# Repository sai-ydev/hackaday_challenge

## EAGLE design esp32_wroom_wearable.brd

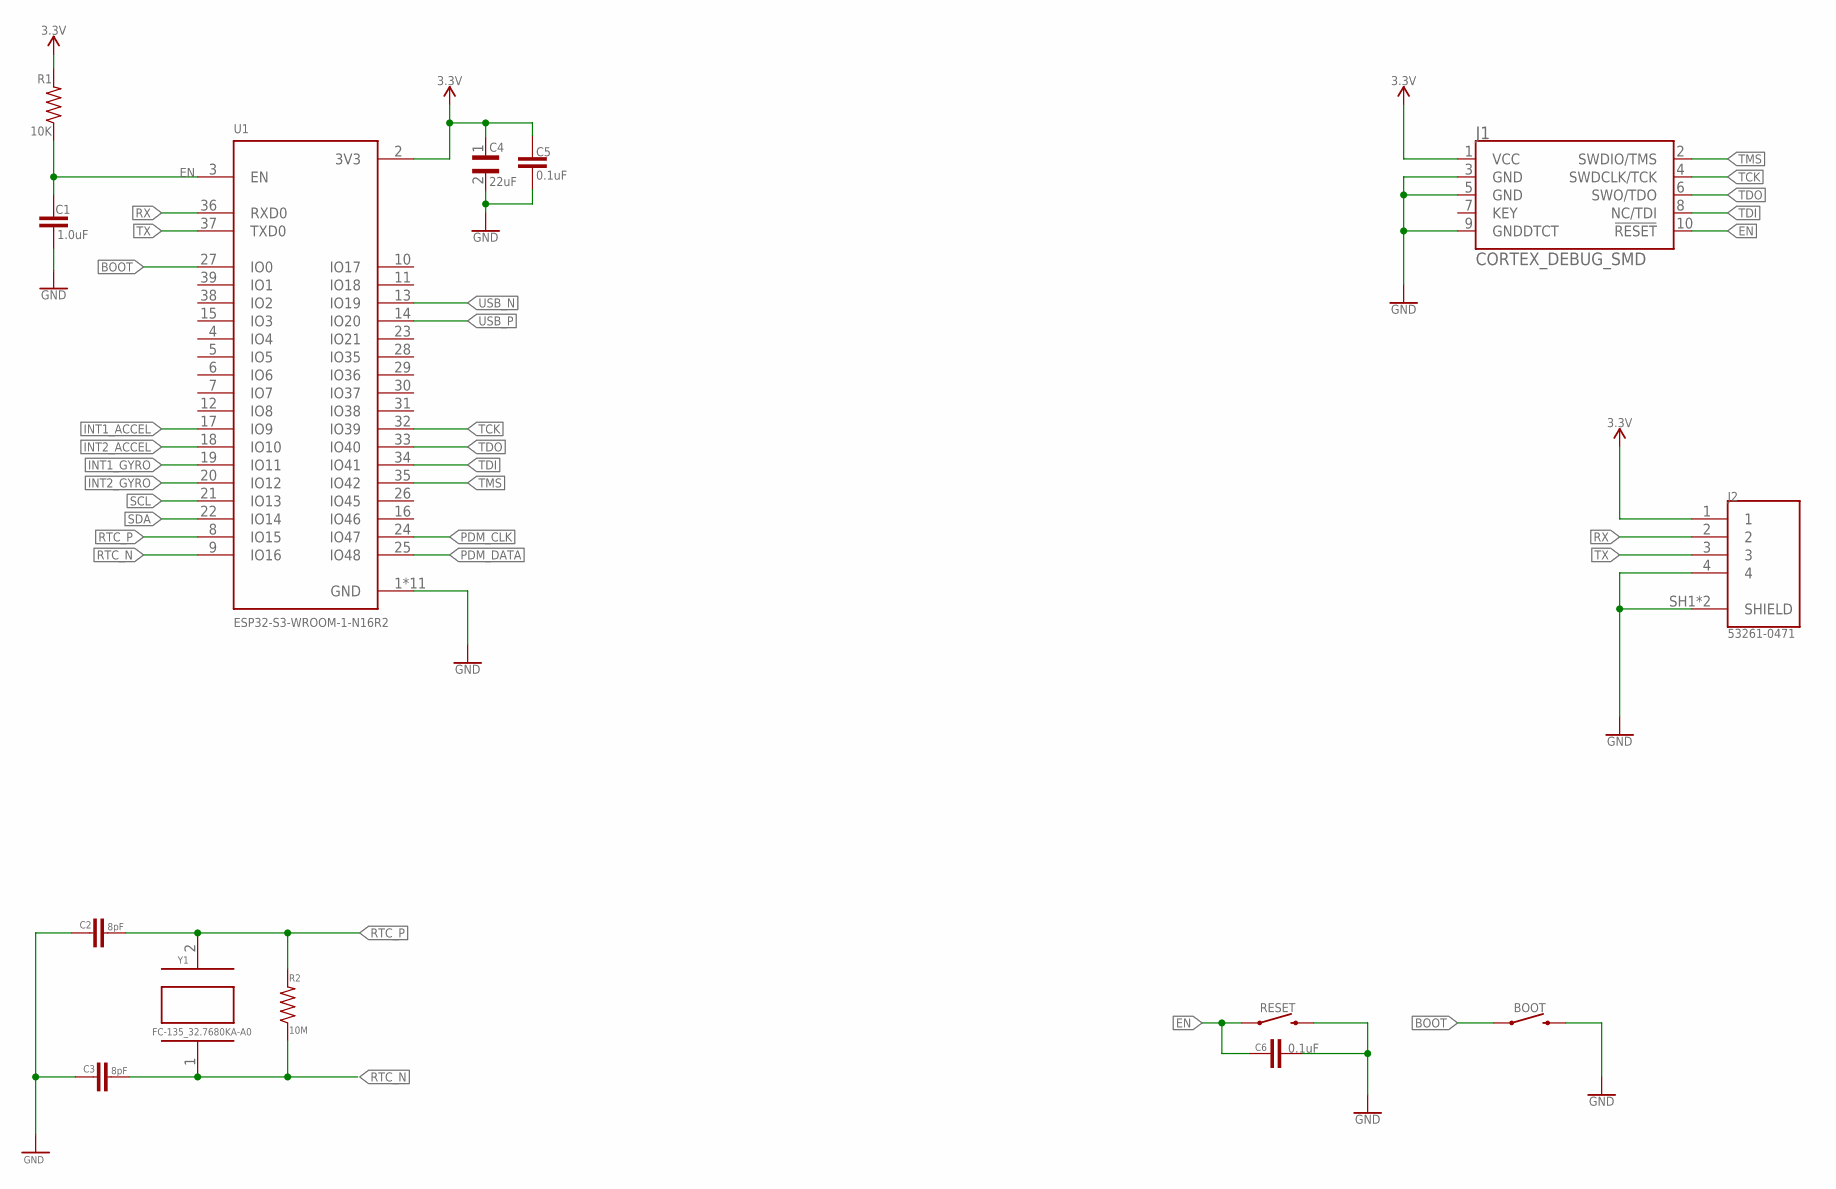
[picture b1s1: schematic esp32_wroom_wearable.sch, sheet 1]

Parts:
BOOT: MOMENTARY-SWITCH-SPST-SMD-4.6X2.8MM; TACTILE_SWITCH_SMD_4.6X2.8MM
C1: 1.0uF; 0402
C2, C3: 8pF; 0402
C4: 22uF; CAPC1005X71N
C5, C6: 0.1uF; 0402
J1: CORTEX_DEBUG_SMD; SAMTECH_FTSH-105-01
J2: 53261-0471; MOLEX_53261-0471
R1: 10K; 0402
R2: 10M; 0402
RESET: MOMENTARY-SWITCH-SPST-SMD-4.6X2.8MM; TACTILE_SWITCH_SMD_4.6X2.8MM
U1: ESP32-S3-WROOM-1-N16R2; XCVR_ESP32-S3-WROOM-1-N16R2
Y1: FC-135_32.7680KA-A0; XTAL_FC-135_32.7680KA-A0

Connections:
3.3V: C4.1, C5.1, J1.1 (VCC), J2.1, R1.2, U1.2 (3V3); also elsewhere on the board
BOOT: BOOT.1, BOOT.2 (1), U1.27 (IO0)
EN: C1.1, C6.1, J1.10 (!RESET), R1.1, RESET.1, RESET.2 (1), U1.3 (EN)
GND: BOOT.3 (2), BOOT.4 (2), C1.2, C2.1, C3.1, C4.2, C5.2, C6.2, J1.3 (GND), J1.5 (GND), J1.9 (GNDDTCT), J2.4, J2.SH1 (SHIELD), J2.SH2 (SHIELD), RESET.3 (2), RESET.4 (2), U1.1 (GND), U1.40 (GND), U1.41_1 (GND), U1.41_2 (GND), U1.41_3 (GND), U1.41_4 (GND), U1.41_5 (GND), U1.41_6 (GND), U1.41_7 (GND), U1.41_8 (GND), U1.41_9 (GND); also elsewhere on the board
INT1_ACCEL: U1.17 (IO9); also elsewhere on the board
INT1_GYRO: U1.19 (IO11); also elsewhere on the board
INT2_ACCEL: U1.18 (IO10); also elsewhere on the board
INT2_GYRO: U1.20 (IO12); also elsewhere on the board
PDM_CLK: U1.24 (IO47); also elsewhere on the board
PDM_DATA: U1.25 (IO48); also elsewhere on the board
RTC_N: C3.2, R2.1, U1.9 (IO16), Y1.1
RTC_P: C2.2, R2.2, U1.8 (IO15), Y1.2
RX: J2.2, U1.36 (RXD0)
SCL: U1.21 (IO13); also elsewhere on the board
SDA: U1.22 (IO14); also elsewhere on the board
TCK: J1.4 (SWDCLK/TCK), U1.32 (IO39)
TDI: J1.8 (NC/TDI), U1.34 (IO41)
TDO: J1.6 (SWO/TDO), U1.33 (IO40)
TMS: J1.2 (SWDIO/TMS), U1.35 (IO42)
TX: J2.3, U1.37 (TXD0)
USB_N: U1.13 (IO19); also elsewhere on the board
USB_P: U1.14 (IO20); also elsewhere on the board

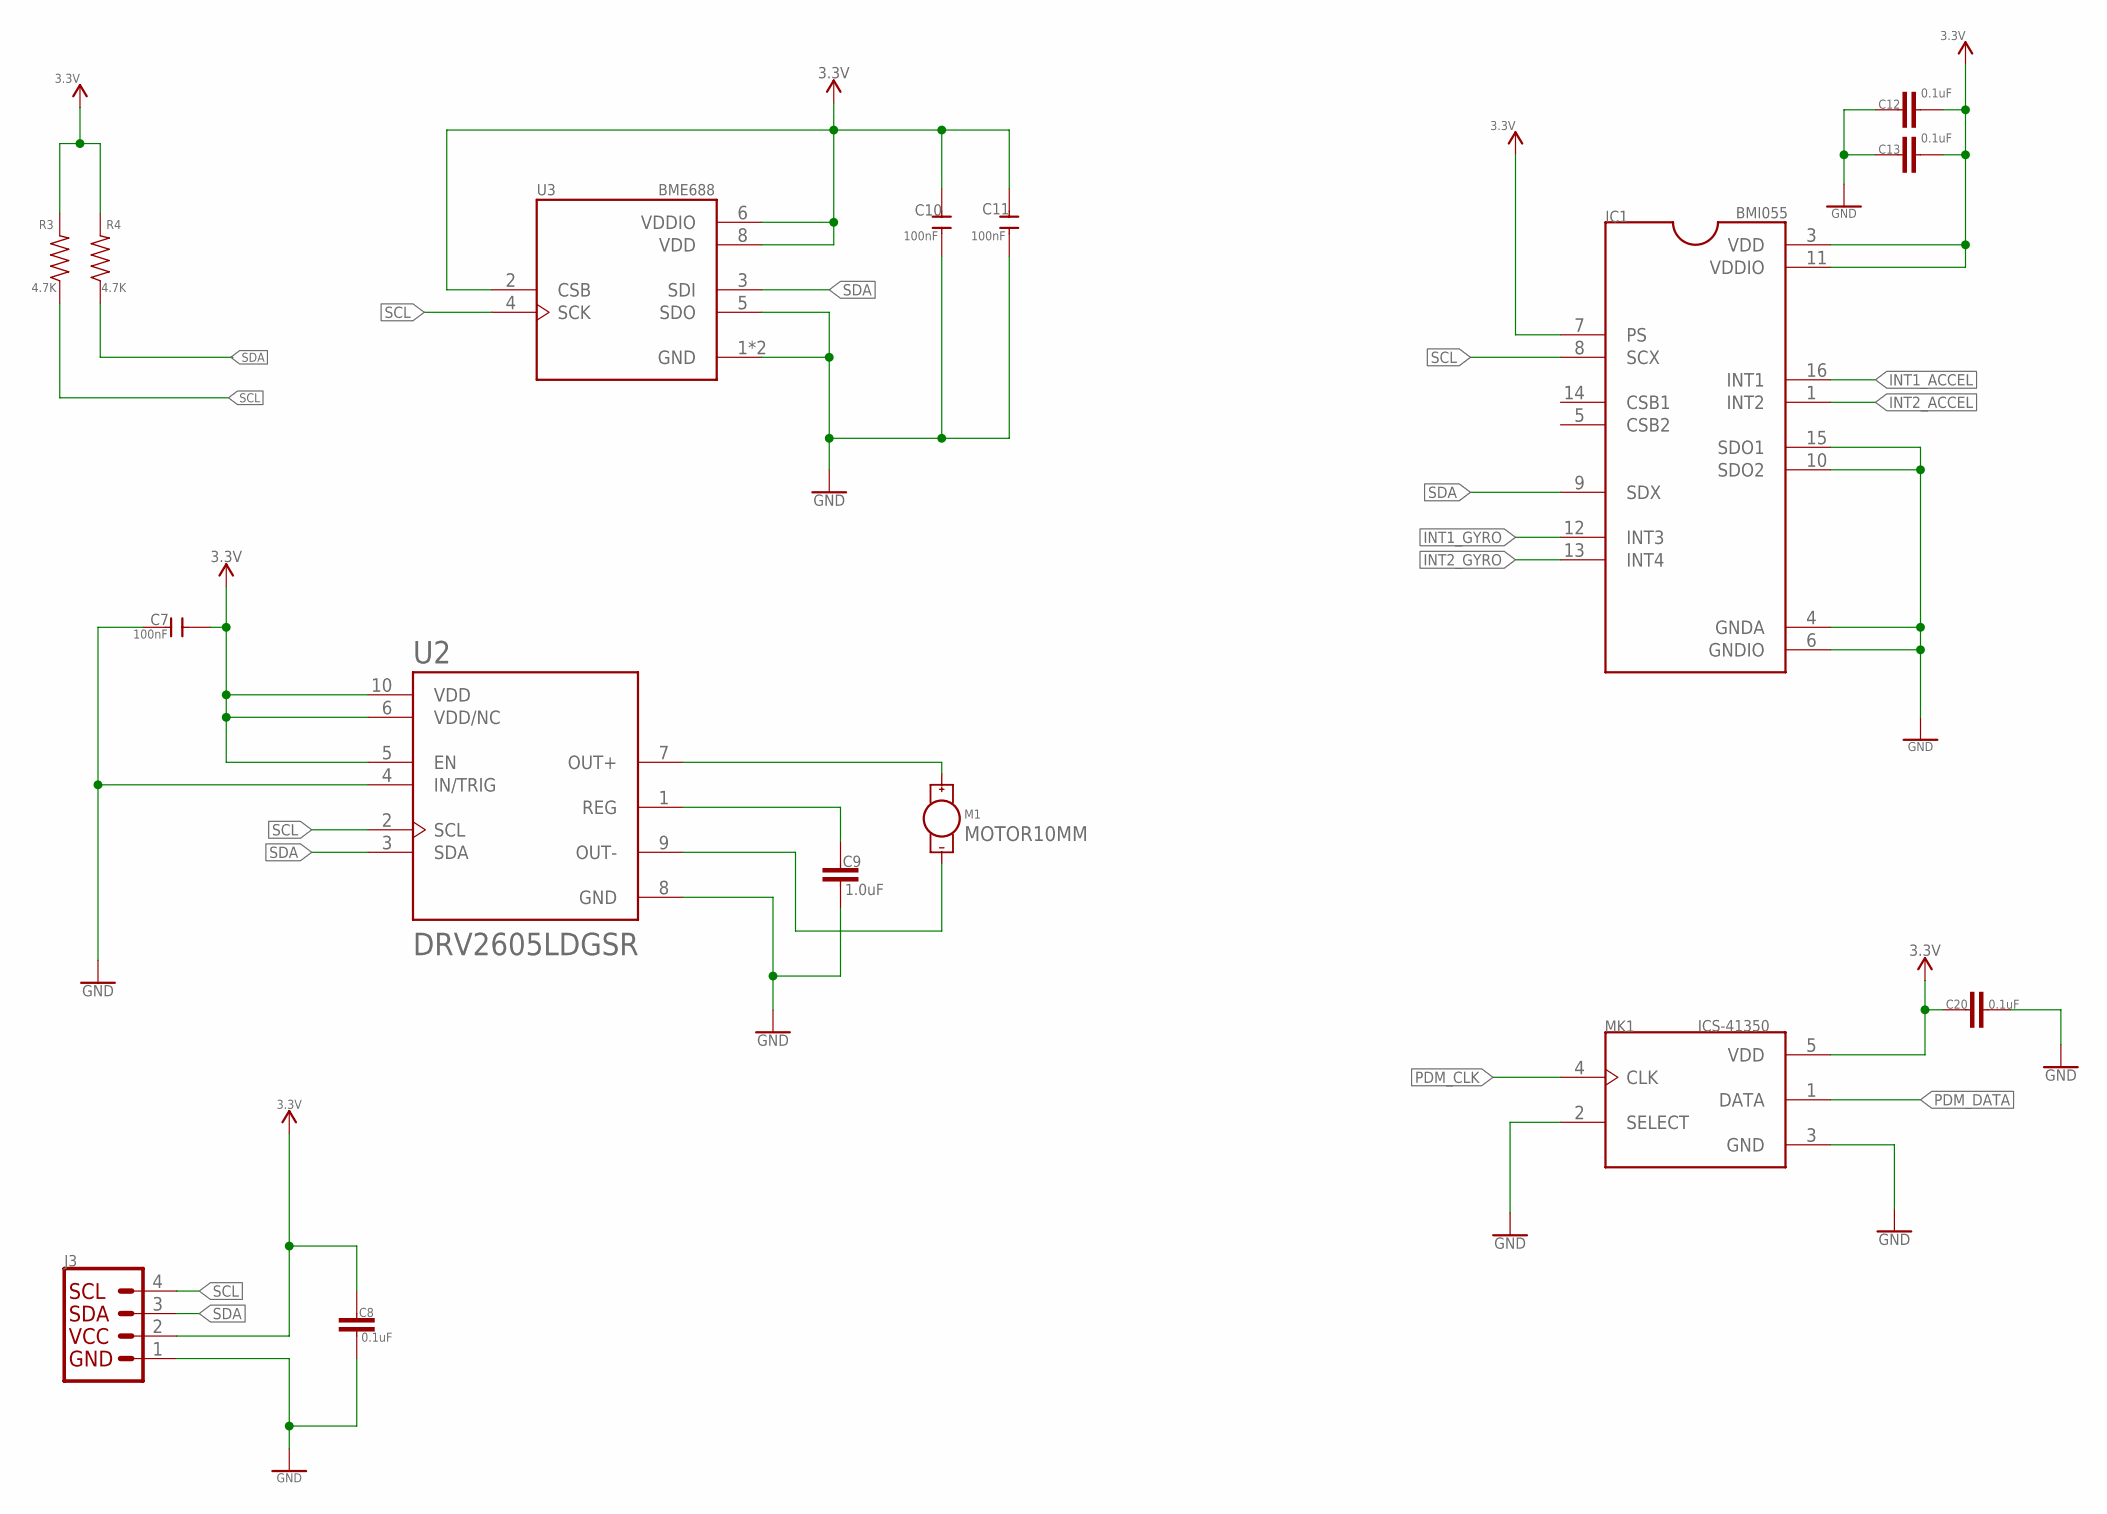
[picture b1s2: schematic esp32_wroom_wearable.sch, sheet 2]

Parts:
C7, C10, C11: 100nF; C0402
C8, C12, C13, C20: 0.1uF; 0402
C9: 1.0uF; 0402
IC1: BMI055; QFN50P300X450X100-16N
J3: QWIIC_CONNECTORJS-1MM; 1X04_1MM_RA
M1: MOTOR10MM; VIBE-MOTOR-10MM
MK1: ICS-41350; MIC_ICS-41350
R3, R4: 4.7K; 0402
U2: DRV2605LDGSR; SOP50P490X110-10N
U3: BME688; IC_BME688

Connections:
3.3V: C7.2, C8.1, C10.1, C11.1, C12.2, C13.2, C20.1, IC1.3 (VDD), IC1.7 (PS), IC1.11 (VDDIO), J3.2, MK1.5 (VDD), R3.2, R4.2, U2.5 (EN), U2.6 (VDD/NC), U2.10 (VDD), U3.2 (CSB), U3.6 (VDDIO), U3.8 (VDD); also elsewhere on the board
GND: C7.1, C8.2, C9.2, C10.2, C11.2, C12.1, C13.1, C20.2, IC1.4 (GNDA), IC1.6 (GNDIO), IC1.10 (SDO2), IC1.15 (SDO1), J3.1, MK1.2 (SELECT), MK1.3 (GND), U2.4 (IN/TRIG), U2.8 (GND), U3.1 (GND), U3.5 (SDO), U3.7 (GND); also elsewhere on the board
INT1_ACCEL: IC1.16 (INT1); also elsewhere on the board
INT1_GYRO: IC1.12 (INT3); also elsewhere on the board
INT2_ACCEL: IC1.1 (INT2); also elsewhere on the board
INT2_GYRO: IC1.13 (INT4); also elsewhere on the board
unnamed: C9.1, U2.1 (REG)
unnamed: M1.+, U2.7 (OUT+)
unnamed: M1.-, U2.9 (OUT-)
PDM_CLK: MK1.4 (CLK); also elsewhere on the board
PDM_DATA: MK1.1 (DATA); also elsewhere on the board
SCL: IC1.8 (SCX), J3.4, R3.1, U2.2 (SCL), U3.4 (SCK); also elsewhere on the board
SDA: IC1.9 (SDX), J3.3, R4.1, U2.3 (SDA), U3.3 (SDI); also elsewhere on the board

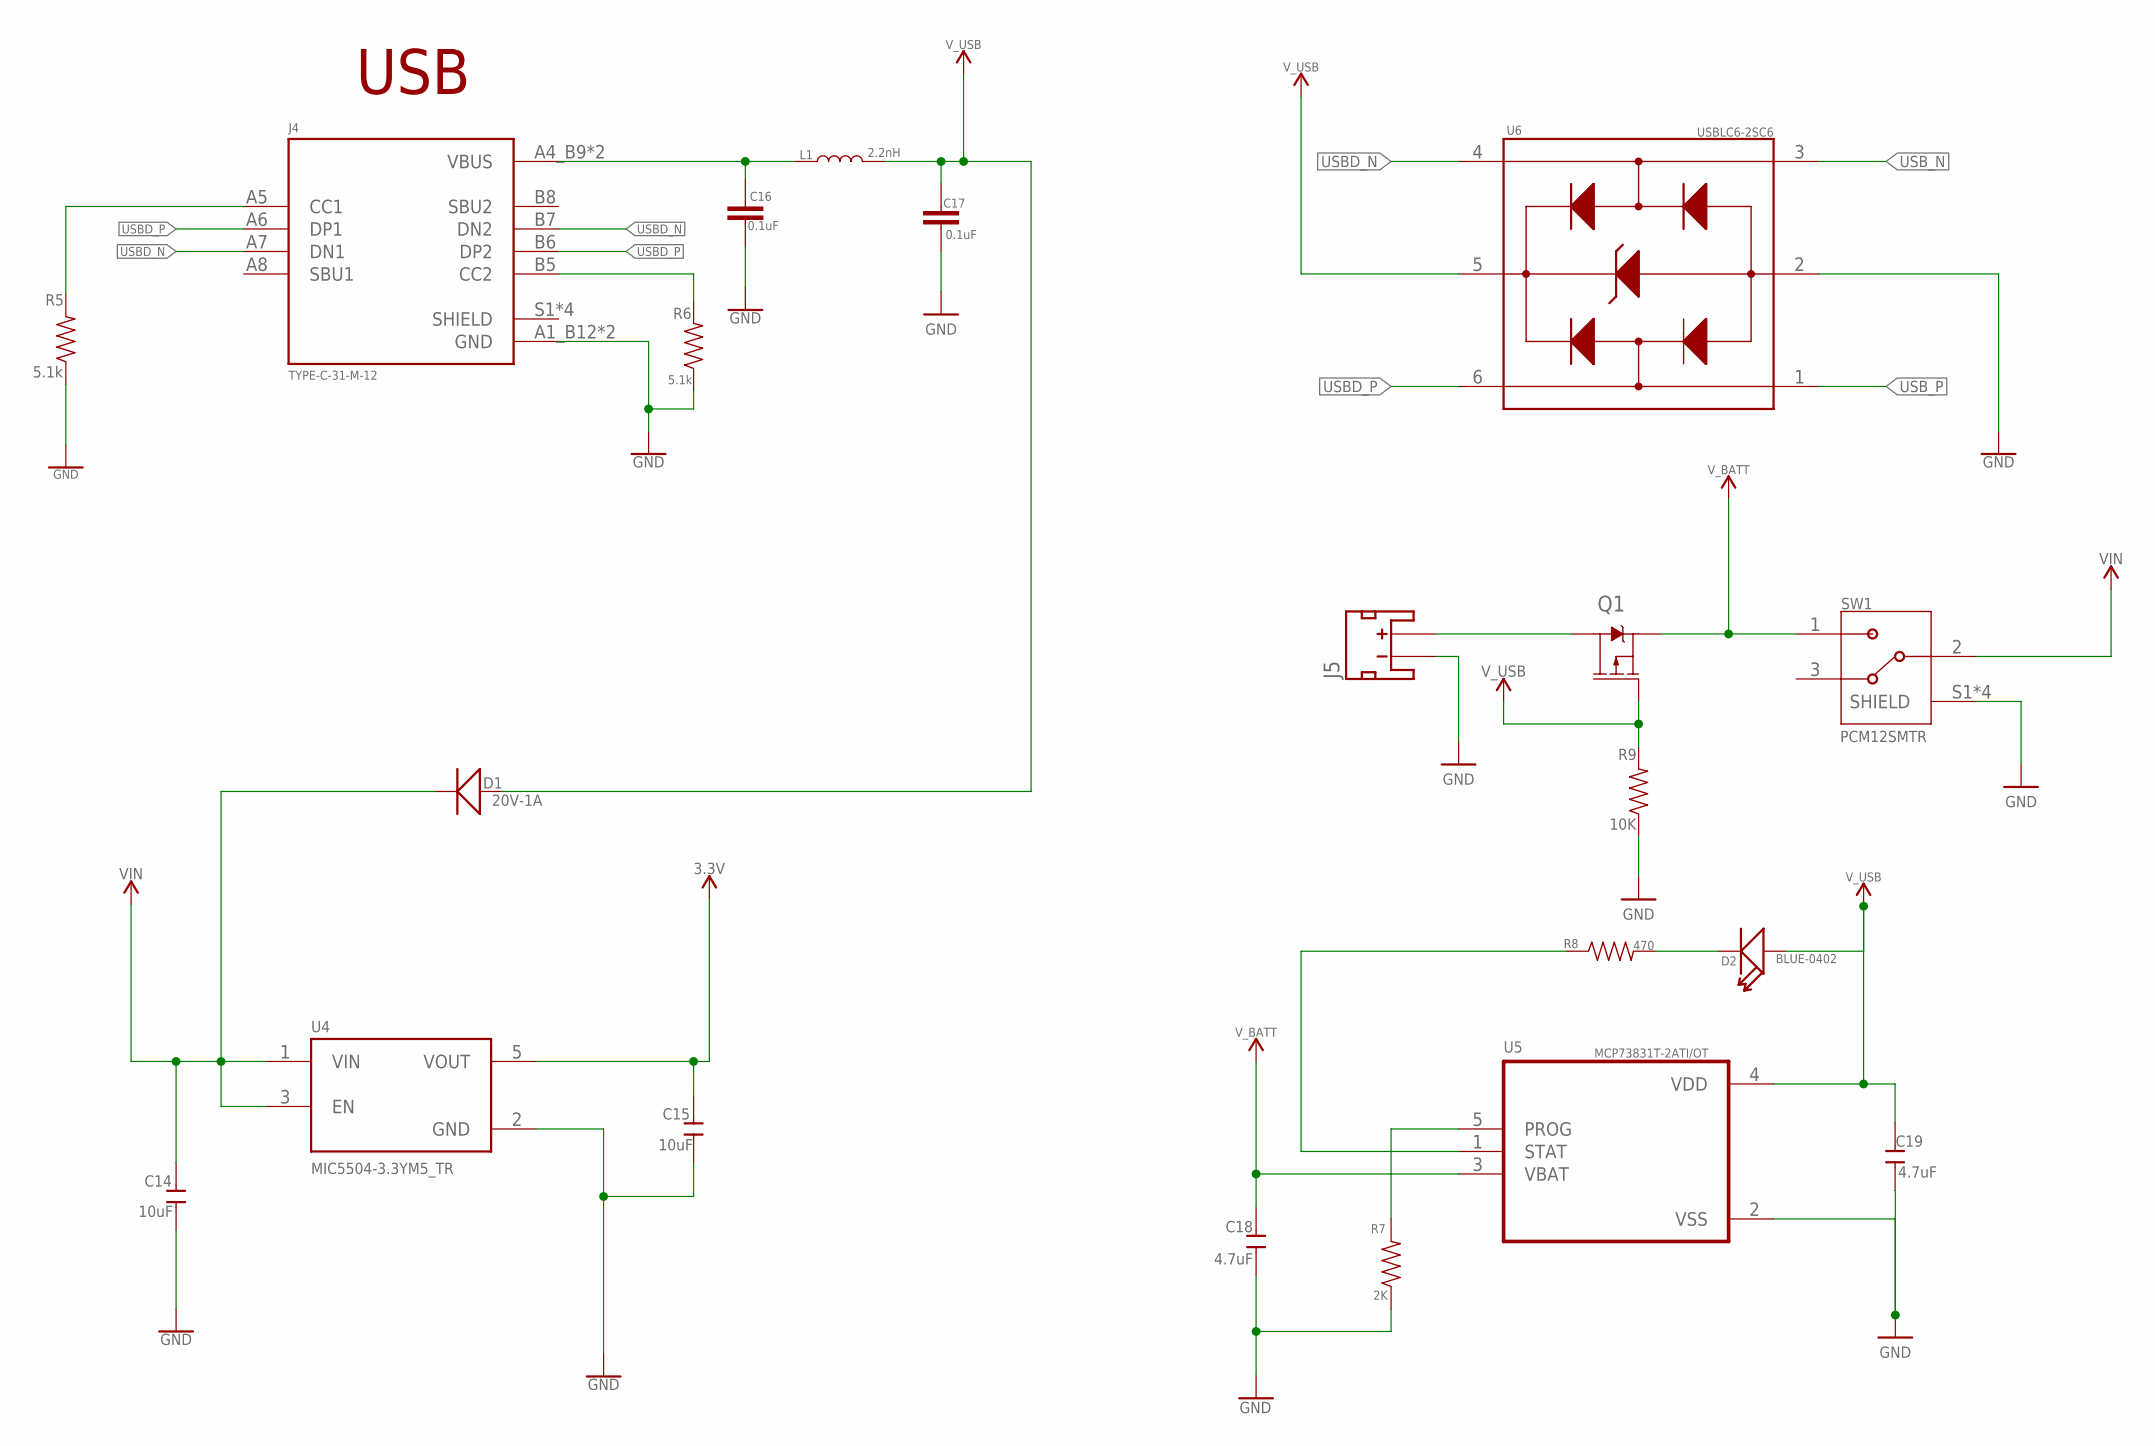
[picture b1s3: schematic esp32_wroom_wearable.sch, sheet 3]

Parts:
C14, C15: 10uF; C0402
C16, C17: 0.1uF; 0402
C18, C19: 4.7uF; C0402
D1: 20V-1A; SOD-123
D2: BLUE-0402; LED-0402
J4: TYPE-C-31-M-12; HRO_TYPE-C-31-M-12
J5: JST_2MM_MALE; JST-2-SMD
L1: 2.2nH; 0402
Q1: 2.5A/30V/105mΩ; SOT23-3
R5, R6: 5.1k; 0603
R7: 2K; 0402
R8: 470; 0402
R9: 10K; 0402
SW1: PCM12SMTR; SW_PCM12SMTR
U4: MIC5504-3.3YM5_TR; SOT95P280X145-5N
U5: MCP73831T-2ATI/OT; SOT95P280X145-5N
U6: USBLC6-2SC6; SOT95P280X145-6N

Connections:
3.3V: C15.2, U4.5 (VOUT); also elsewhere on the board
GND: C14.1, C15.1, C16.2, C17.2, C18.1, C19.1, J4.A1_B12 (GND), J4.B1_A12 (GND), J5.1 (-), R5.1, R6.1, R7.1, R9.1, SW1.S1 (SHIELD), SW1.S2 (SHIELD), SW1.S3 (SHIELD), SW1.S4 (SHIELD), U4.2 (GND), U5.2 (VSS), U6.2 (GND); also elsewhere on the board
unnamed: J4.A5 (CC1), R5.2
unnamed: J4.B5 (CC2), R6.2
unnamed: J5.2 (+), Q1.3 (D)
unnamed: D2.-, R8.2
unnamed: R8.1, U5.1 (STAT)
unnamed: C16.1, J4.A4_B9 (VBUS), J4.B4_A9 (VBUS), L1.1
unnamed: R7.2, U5.5 (PROG)
USBD_N: J4.A7 (DN1), J4.B7 (DN2), U6.4 (I/O2_OUT)
USBD_P: J4.A6 (DP1), J4.B6 (DP2), U6.6 (I/O1_OUT)
USB_N: U6.3 (I/O2_IN); also elsewhere on the board
USB_P: U6.1 (I/O1_IN); also elsewhere on the board
VIN: C14.2, D1.-, SW1.2, U4.1 (VIN), U4.3 (EN)
V_BATT: C18.2, Q1.2 (S), SW1.1, U5.3 (VBAT)
V_USB: C17.1, C19.2, D1.+, D2.+, L1.2, Q1.1 (G), R9.2, U5.4 (VDD), U6.5 (VBUS)

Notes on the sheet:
USB

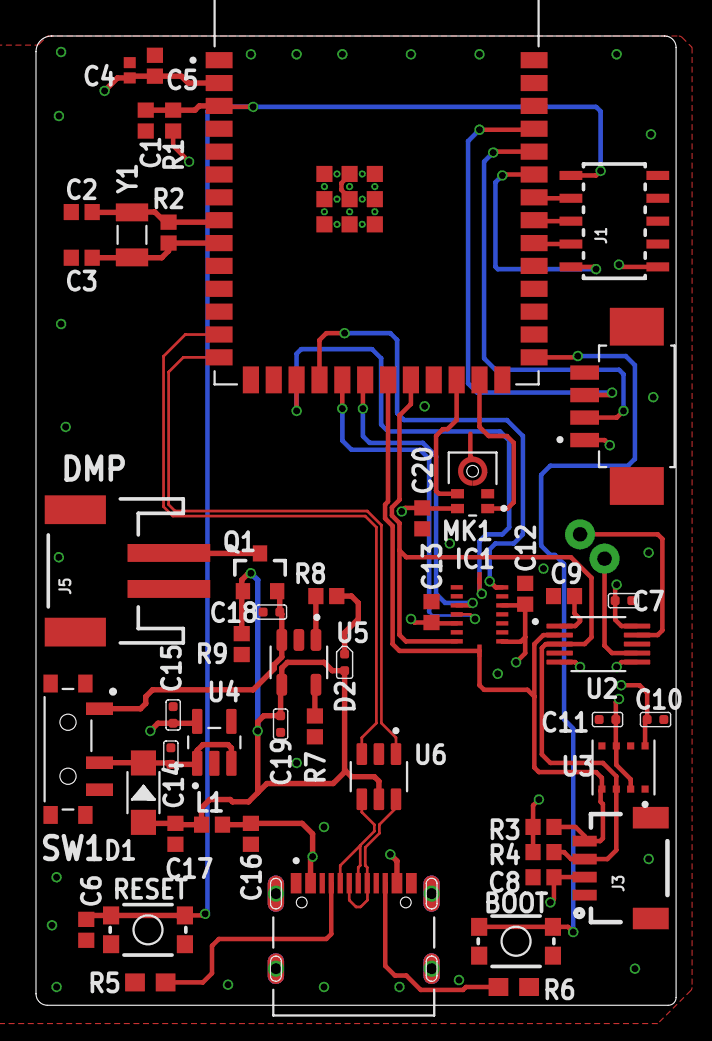
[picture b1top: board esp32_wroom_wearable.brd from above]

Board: 4 copper layers, 35.6 x 53.8 mm, 51 parts (1 on the bottom side), 37 nets.

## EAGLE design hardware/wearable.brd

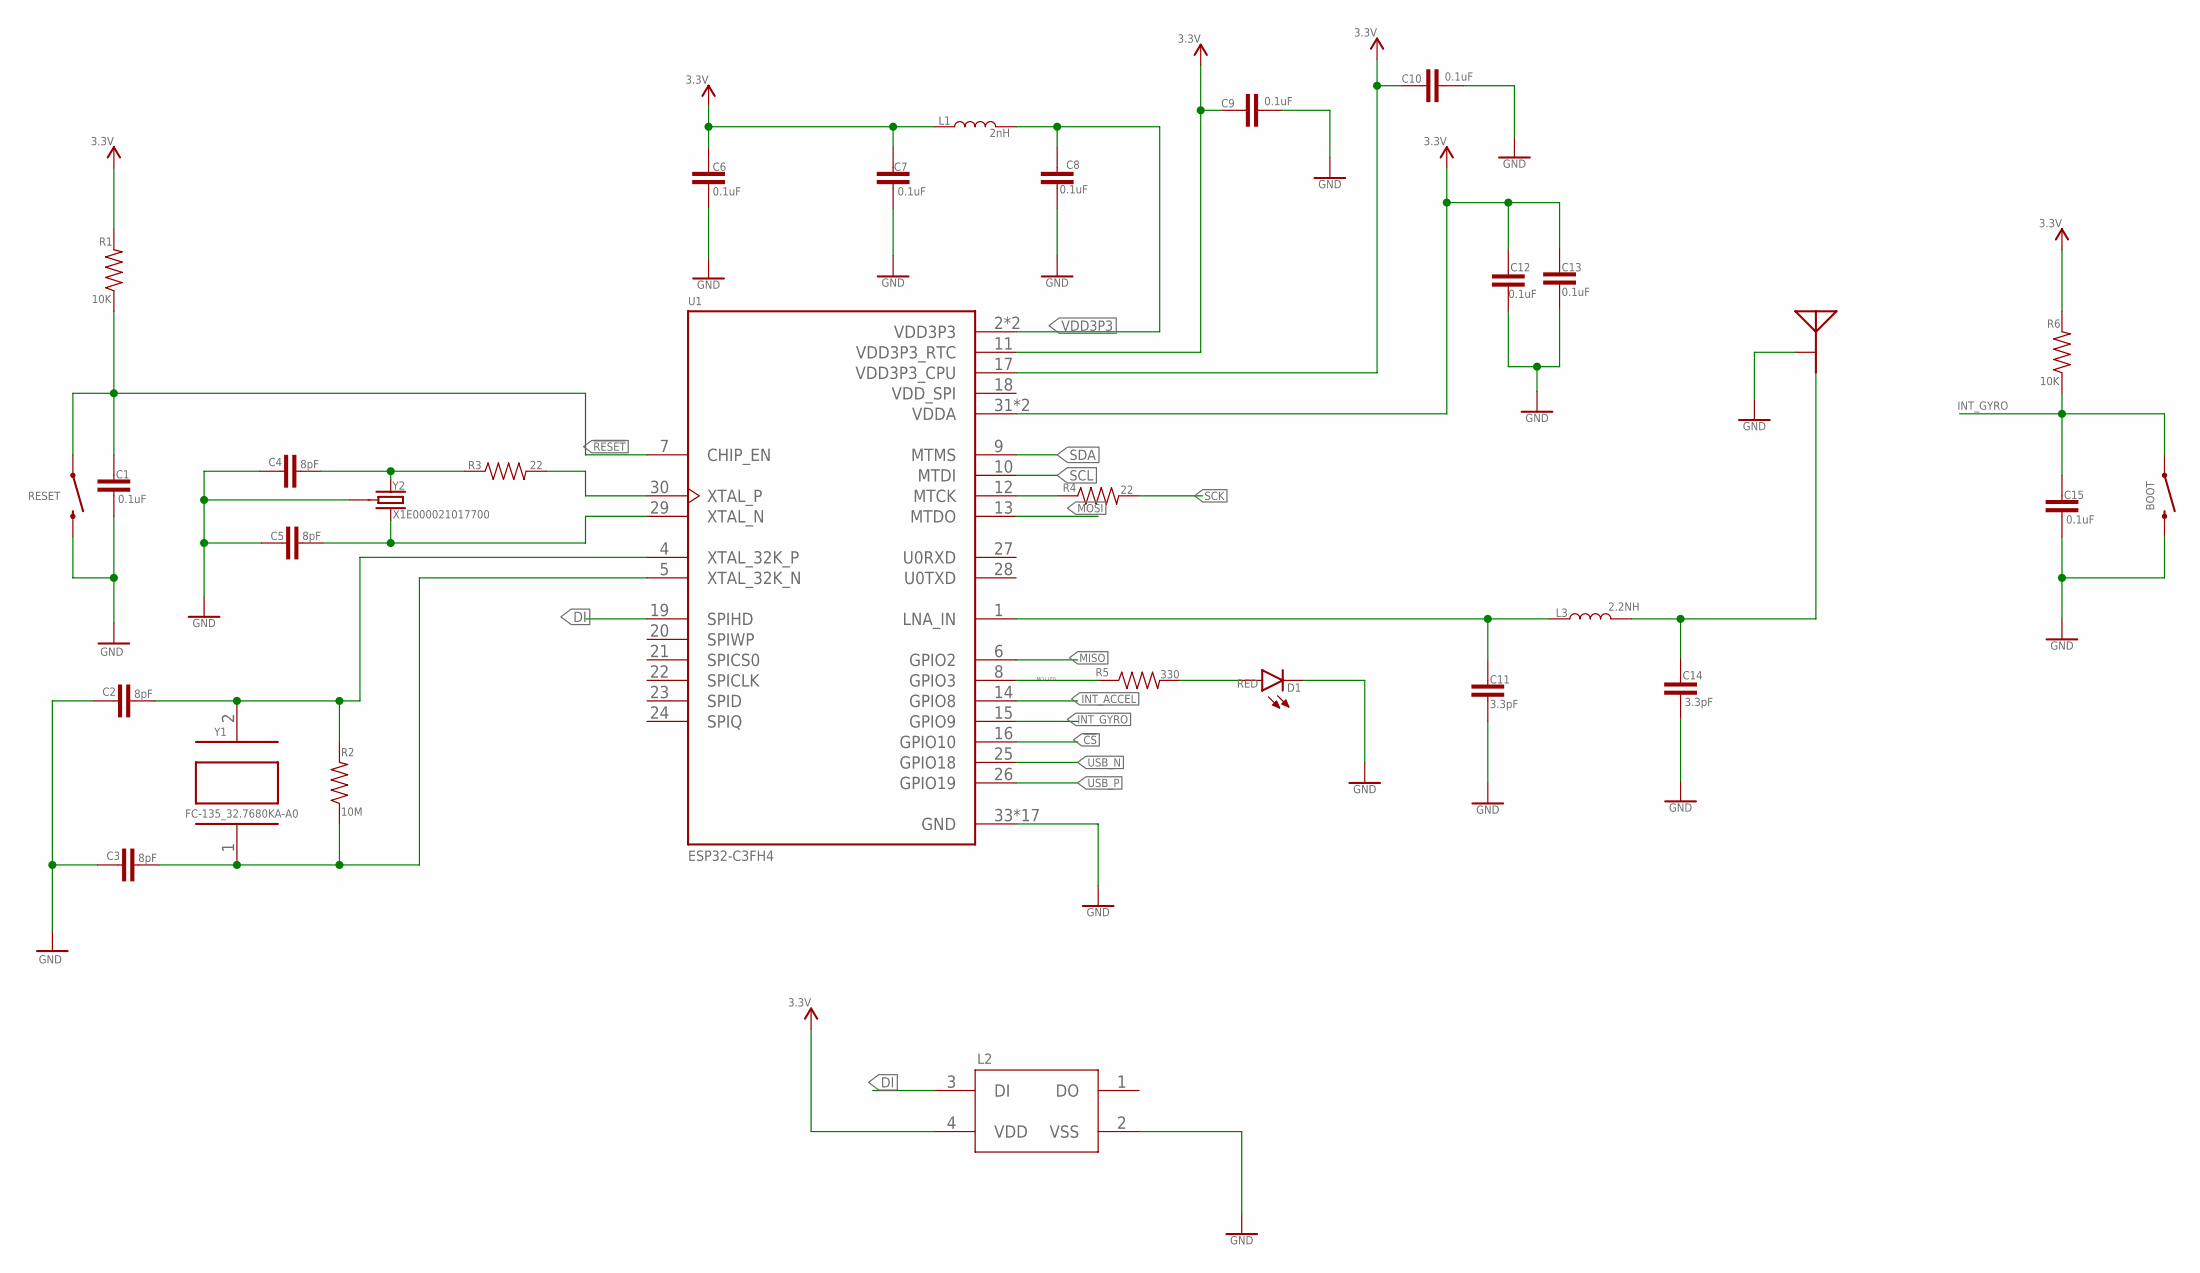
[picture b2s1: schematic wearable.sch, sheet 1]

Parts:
ANT1: MEANDER-ANT
BOOT: MOMENTARY-SWITCH-SPST-SMD-4.6X2.8MM; TACTILE_SWITCH_SMD_4.6X2.8MM
C1, C6, C7, C8, C9, C10, C12, C13, C15: 0.1uF; 0402
C2, C3, C4, C5: 8pF; 0402
C11, C14: 3.3pF; 0402
D1: RED; LED-0603
L1: 2nH; 0402
L2: WS2812B-2020
L3: 2.2NH; 0402
R1, R6: 10K; 0402
R2: 10M; 0402
R3, R4: 22; 0402
R5: 330; 0402
RESET: MOMENTARY-SWITCH-SPST-SMD-4.6X2.8MM; TACTILE_SWITCH_SMD_4.6X2.8MM
U1: ESP32-C3FH4; QFN50P500X500X90-33N
Y1: FC-135_32.7680KA-A0; XTAL_FC-135_32.7680KA-A0
Y2: X1E000021017700; CRYSTAL-SMD-3.2X2.5MM

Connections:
3.3V: C6.1, C7.2, C9.2, C10.2, C12.1, C13.1, L1.1, L2.4 (VDD), R1.2, R6.2, U1.11 (VDD3P3_RTC), U1.17 (VDD3P3_CPU), U1.31 (VDDA), U1.32 (VDDA); also elsewhere on the board
!CS: U1.16 (GPIO10); also elsewhere on the board
!RESET: C1.1, R1.1, RESET.1, RESET.2 (1), U1.7 (CHIP_EN)
DI: L2.3 (DI), U1.19 (SPIHD)
GND: ANT1.GND, BOOT.3 (2), BOOT.4 (2), C1.2, C2.1, C3.1, C4.1, C5.1, C6.2, C7.1, C8.1, C9.1, C10.1, C11.2, C12.2, C13.2, C14.2, C15.2, D1.C, L2.2 (VSS), RESET.3 (2), RESET.4 (2), U1.33 (GND), U1.34 (GND), U1.35 (GND), U1.36 (GND), U1.37 (GND), U1.38 (GND), U1.39 (GND), U1.40 (GND), U1.41 (GND), U1.42 (GND), U1.43 (GND), U1.44 (GND), U1.45 (GND), U1.46 (GND), U1.47 (GND), U1.48 (GND), U1.49 (GND), Y2.2 (3), Y2.4 (3); also elsewhere on the board
INT_ACCEL: U1.14 (GPIO8); also elsewhere on the board
INT_GYRO: BOOT.1, BOOT.2 (1), C15.1, R6.1, U1.15 (GPIO9); also elsewhere on the board
MCU_LED: R5.1, U1.8 (GPIO3)
MISO: U1.6 (GPIO2); also elsewhere on the board
MOSI: U1.13 (MTDO); also elsewhere on the board
unnamed: R3.2, U1.30 (XTAL_P)
unnamed: C4.2, R3.1, Y2.1
unnamed: C5.2, U1.29 (XTAL_N), Y2.3 (2)
unnamed: C11.1, L3.1, U1.1 (LNA_IN)
unnamed: ANT1.FEED, C14.1, L3.2
unnamed: D1.A, R5.2
unnamed: C2.2, R2.2, U1.4 (XTAL_32K_P), Y1.2
unnamed: C3.2, R2.1, U1.5 (XTAL_32K_N), Y1.1
unnamed: R4.1, U1.12 (MTCK)
SCK: R4.2; also elsewhere on the board
SCL: U1.10 (MTDI); also elsewhere on the board
SDA: U1.9 (MTMS); also elsewhere on the board
USB_N: U1.25 (GPIO18); also elsewhere on the board
USB_P: U1.26 (GPIO19); also elsewhere on the board
VDD3P3: C8.2, L1.2, U1.2 (VDD3P3), U1.3 (VDD3P3)
VDD_SPI: U1.18 (VDD_SPI)

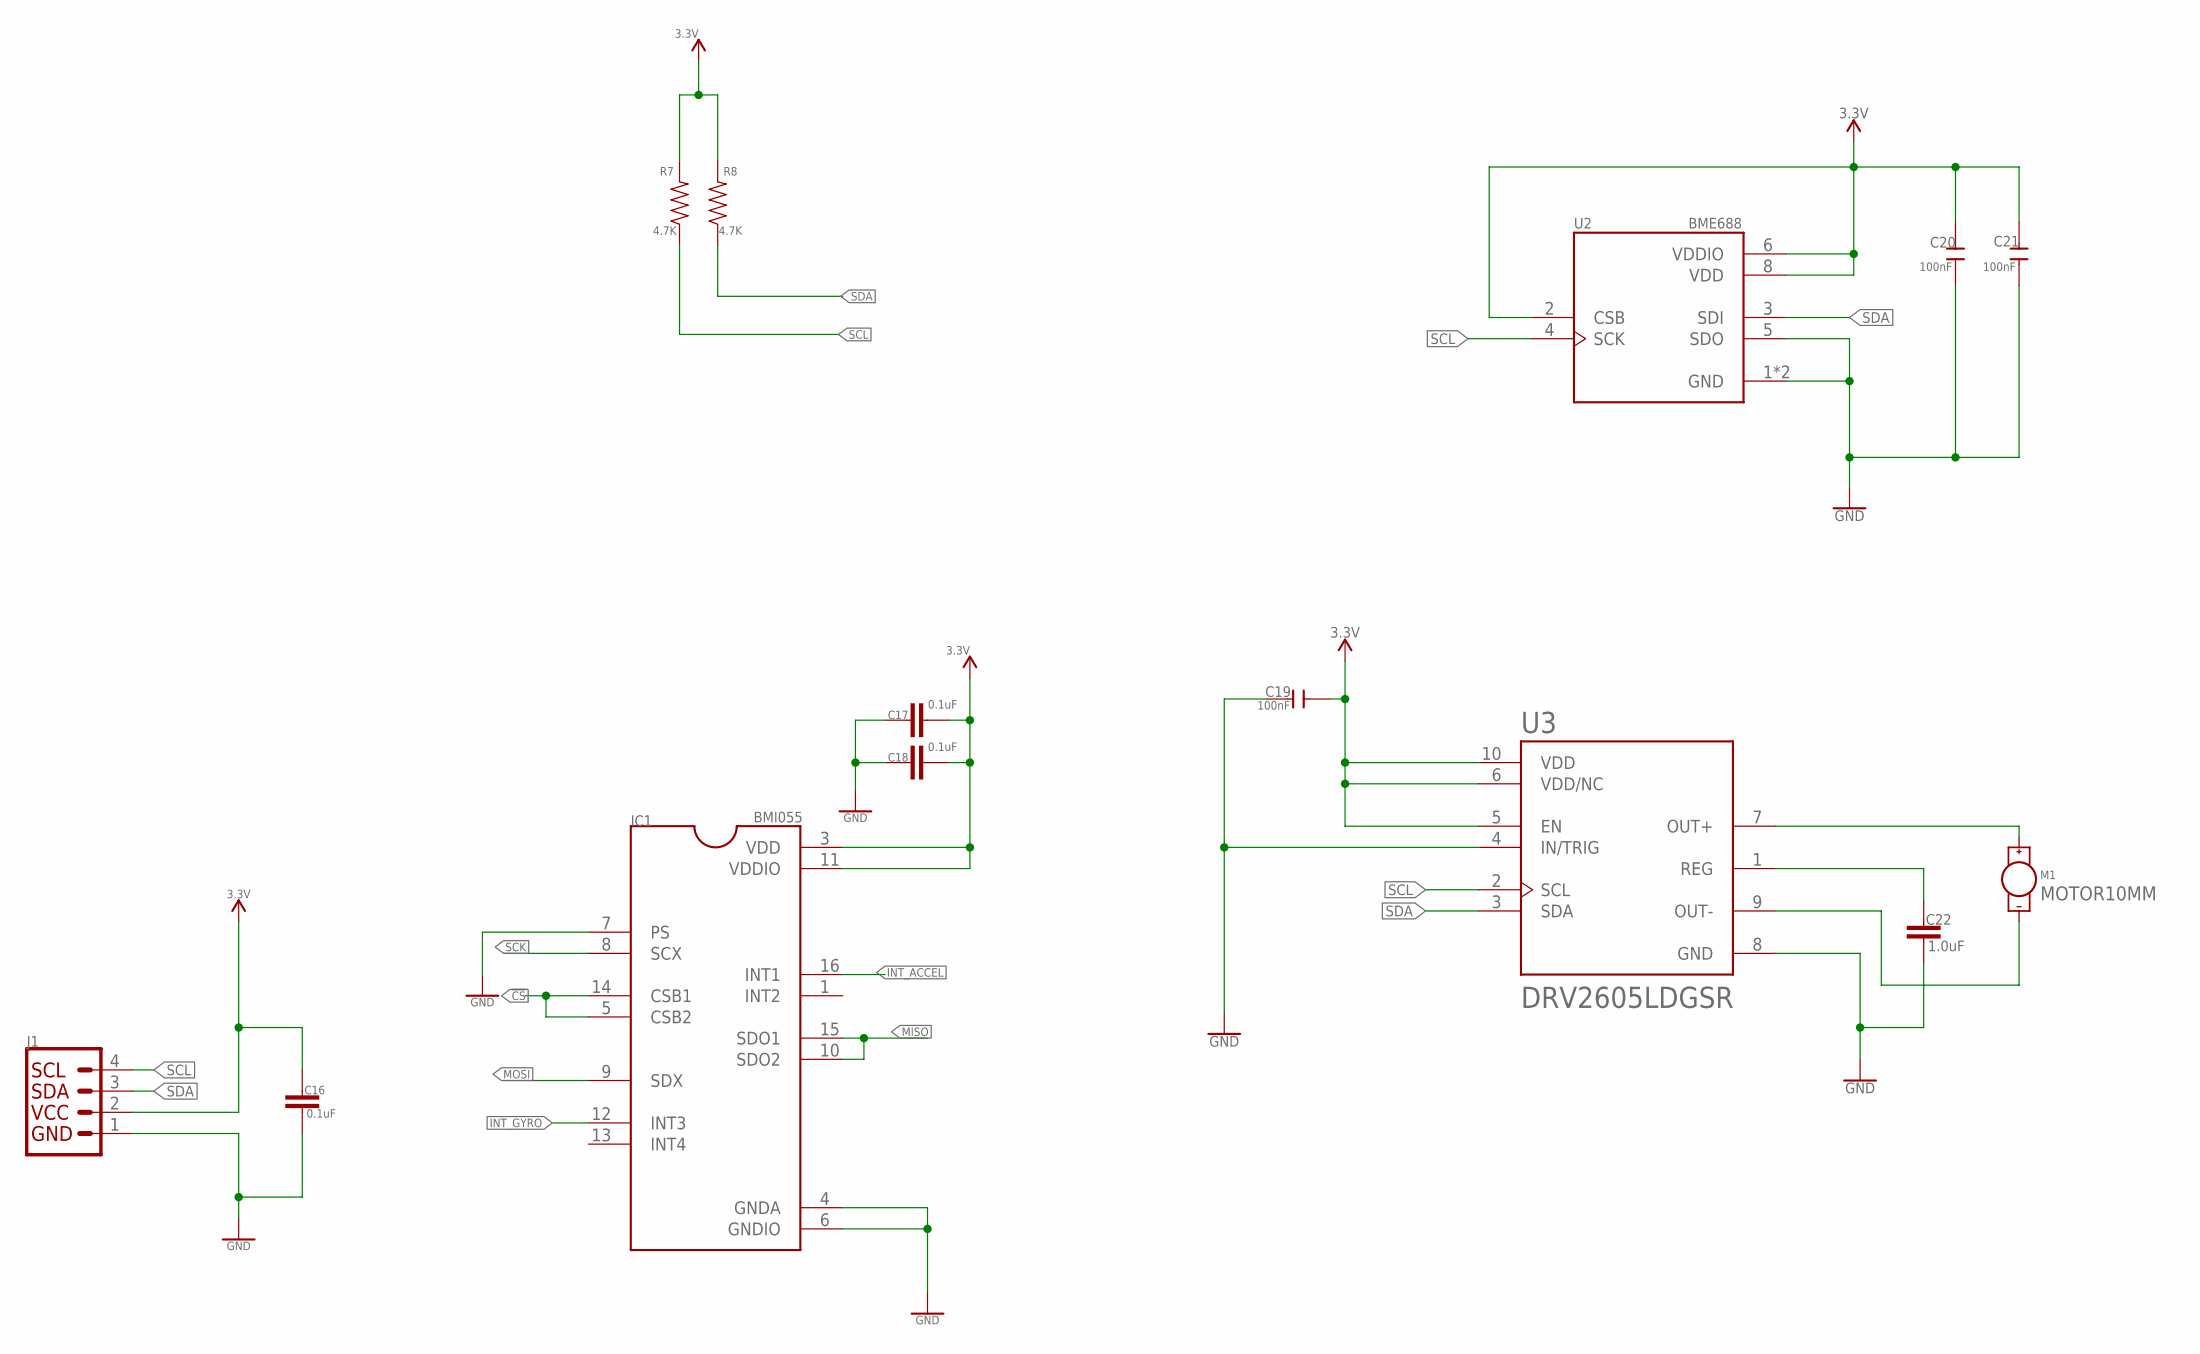
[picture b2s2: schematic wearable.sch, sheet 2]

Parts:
C16, C17, C18: 0.1uF; 0402
C19, C20, C21: 100nF; C0402
C22: 1.0uF; 0402
IC1: BMI055; QFN50P300X450X100-16N
J1: QWIIC_CONNECTORJS-1MM; 1X04_1MM_RA
M1: MOTOR10MM; VIBE-MOTOR-10MM
R7, R8: 4.7K; 0402
U2: BME688; IC_BME688
U3: DRV2605LDGSR; SOP50P490X110-10N

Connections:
3.3V: C16.1, C17.2, C18.2, C19.2, C20.1, C21.1, IC1.3 (VDD), IC1.11 (VDDIO), J1.2, R7.2, R8.2, U2.2 (CSB), U2.6 (VDDIO), U2.8 (VDD), U3.5 (EN), U3.6 (VDD/NC), U3.10 (VDD); also elsewhere on the board
!CS: IC1.5 (CSB2), IC1.14 (CSB1); also elsewhere on the board
GND: C16.2, C17.1, C18.1, C19.1, C20.2, C21.2, C22.2, IC1.4 (GNDA), IC1.6 (GNDIO), IC1.7 (PS), J1.1, U2.1 (GND), U2.5 (SDO), U2.7 (GND), U3.4 (IN/TRIG), U3.8 (GND); also elsewhere on the board
INT_ACCEL: IC1.16 (INT1); also elsewhere on the board
INT_GYRO: IC1.12 (INT3); also elsewhere on the board
MISO: IC1.10 (SDO2), IC1.15 (SDO1); also elsewhere on the board
MOSI: IC1.9 (SDX); also elsewhere on the board
unnamed: C22.1, U3.1 (REG)
unnamed: M1.+, U3.7 (OUT+)
unnamed: M1.-, U3.9 (OUT-)
SCK: IC1.8 (SCX); also elsewhere on the board
SCL: J1.4, R7.1, U2.4 (SCK), U3.2 (SCL); also elsewhere on the board
SDA: J1.3, R8.1, U2.3 (SDI), U3.3 (SDA); also elsewhere on the board

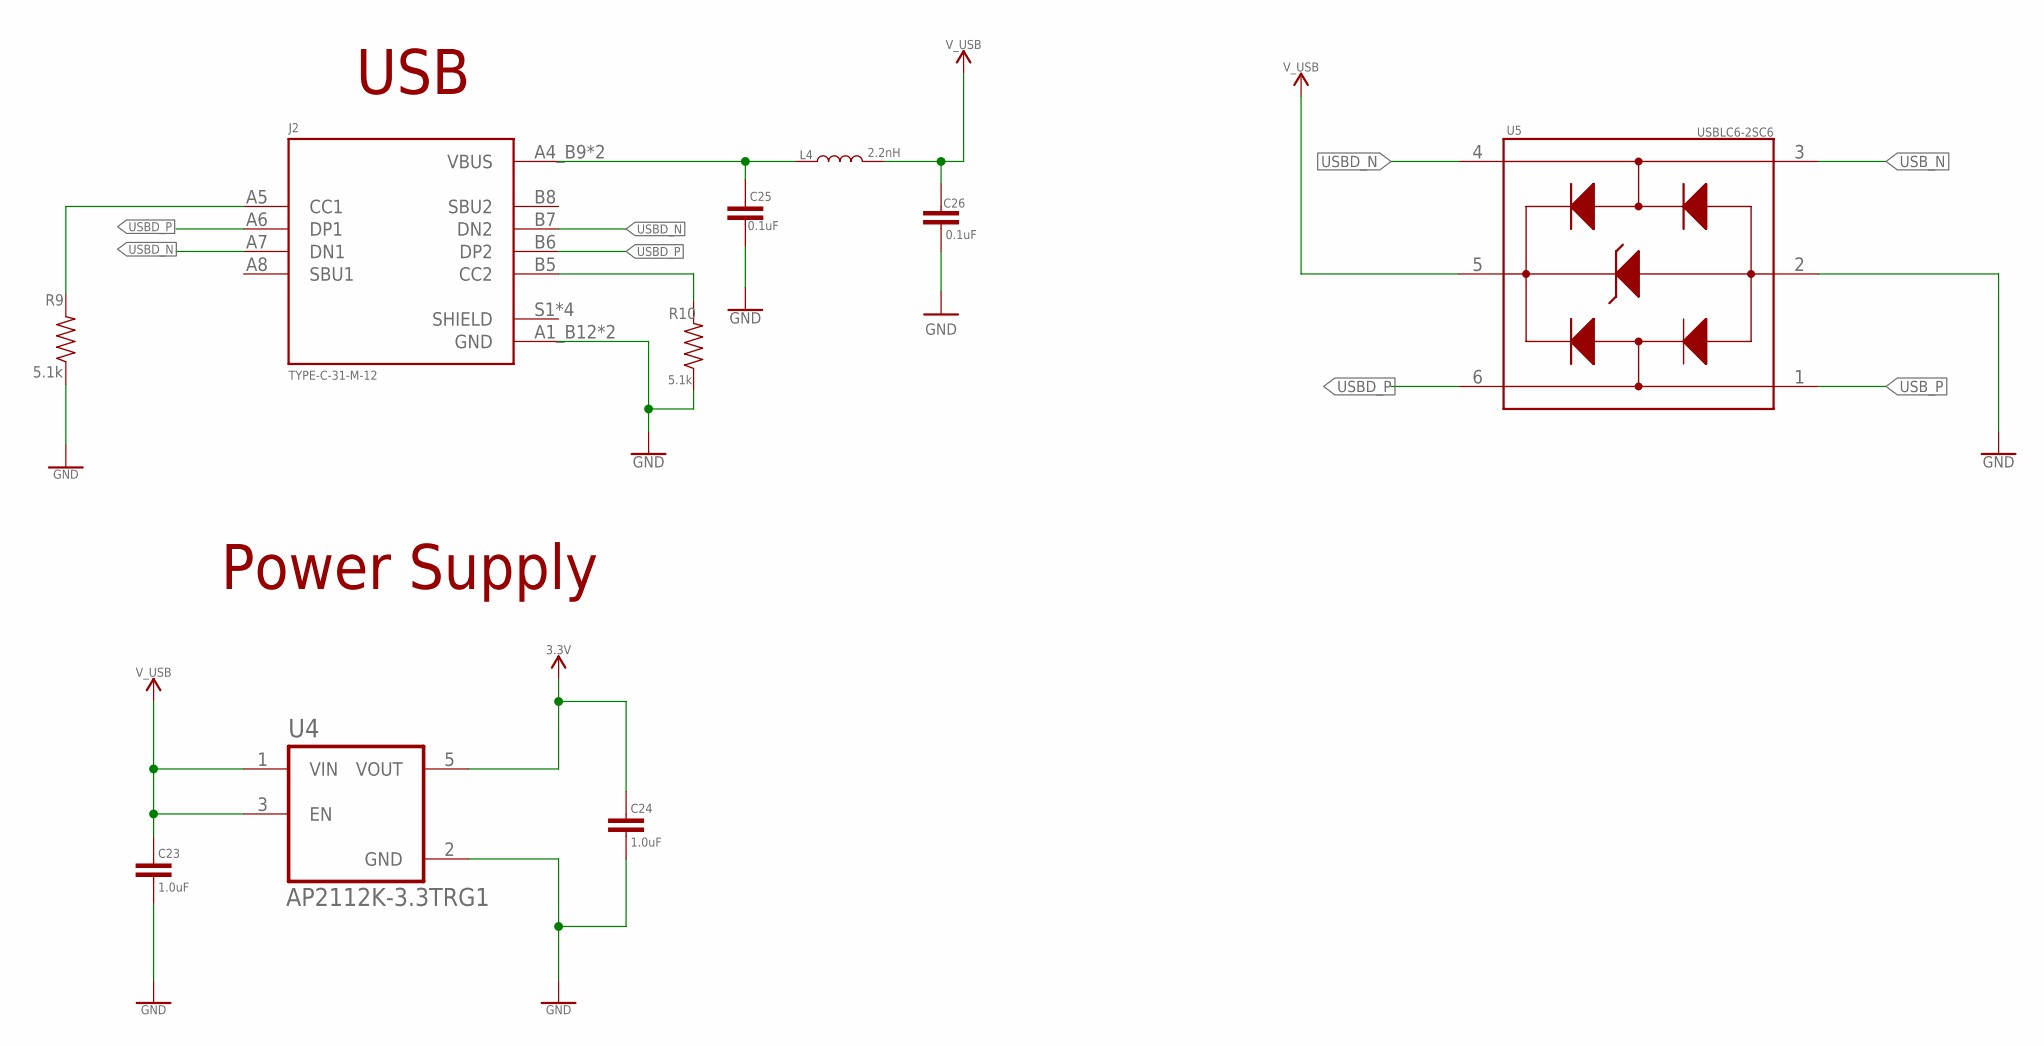
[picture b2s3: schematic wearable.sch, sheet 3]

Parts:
C23, C24: 1.0uF; 0402
C25, C26: 0.1uF; 0402
J2: TYPE-C-31-M-12; HRO_TYPE-C-31-M-12
L4: 2.2nH; 0402
R9, R10: 5.1k; 0603
U4: AP2112K-3.3TRG1; SOT95P285X140-5N
U5: USBLC6-2SC6; SOT95P280X145-6N

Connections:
3.3V: C24.1, U4.5 (VOUT); also elsewhere on the board
GND: C23.2, C24.2, C25.2, C26.2, J2.A1_B12 (GND), J2.B1_A12 (GND), R9.1, R10.1, U4.2 (GND), U5.2 (GND); also elsewhere on the board
unnamed: J2.A5 (CC1), R9.2
unnamed: J2.B5 (CC2), R10.2
unnamed: C25.1, J2.A4_B9 (VBUS), J2.B4_A9 (VBUS), L4.1
USBD_N: J2.A7 (DN1), J2.B7 (DN2), U5.4 (I/O2_OUT)
USBD_P: J2.A6 (DP1), J2.B6 (DP2), U5.6 (I/O1_OUT)
USB_N: U5.3 (I/O2_IN); also elsewhere on the board
USB_P: U5.1 (I/O1_IN); also elsewhere on the board
V_USB: C23.1, C26.1, L4.2, U4.1 (VIN), U4.3 (EN), U5.5 (VBUS)

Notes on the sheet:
Power Supply
USB

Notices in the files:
parts and their libraries:
SparkFun-Capacitors: Licensing: Creative Commons ShareAlike 4.0 International - https://creativecommons.org/licenses/by-sa/4.0
